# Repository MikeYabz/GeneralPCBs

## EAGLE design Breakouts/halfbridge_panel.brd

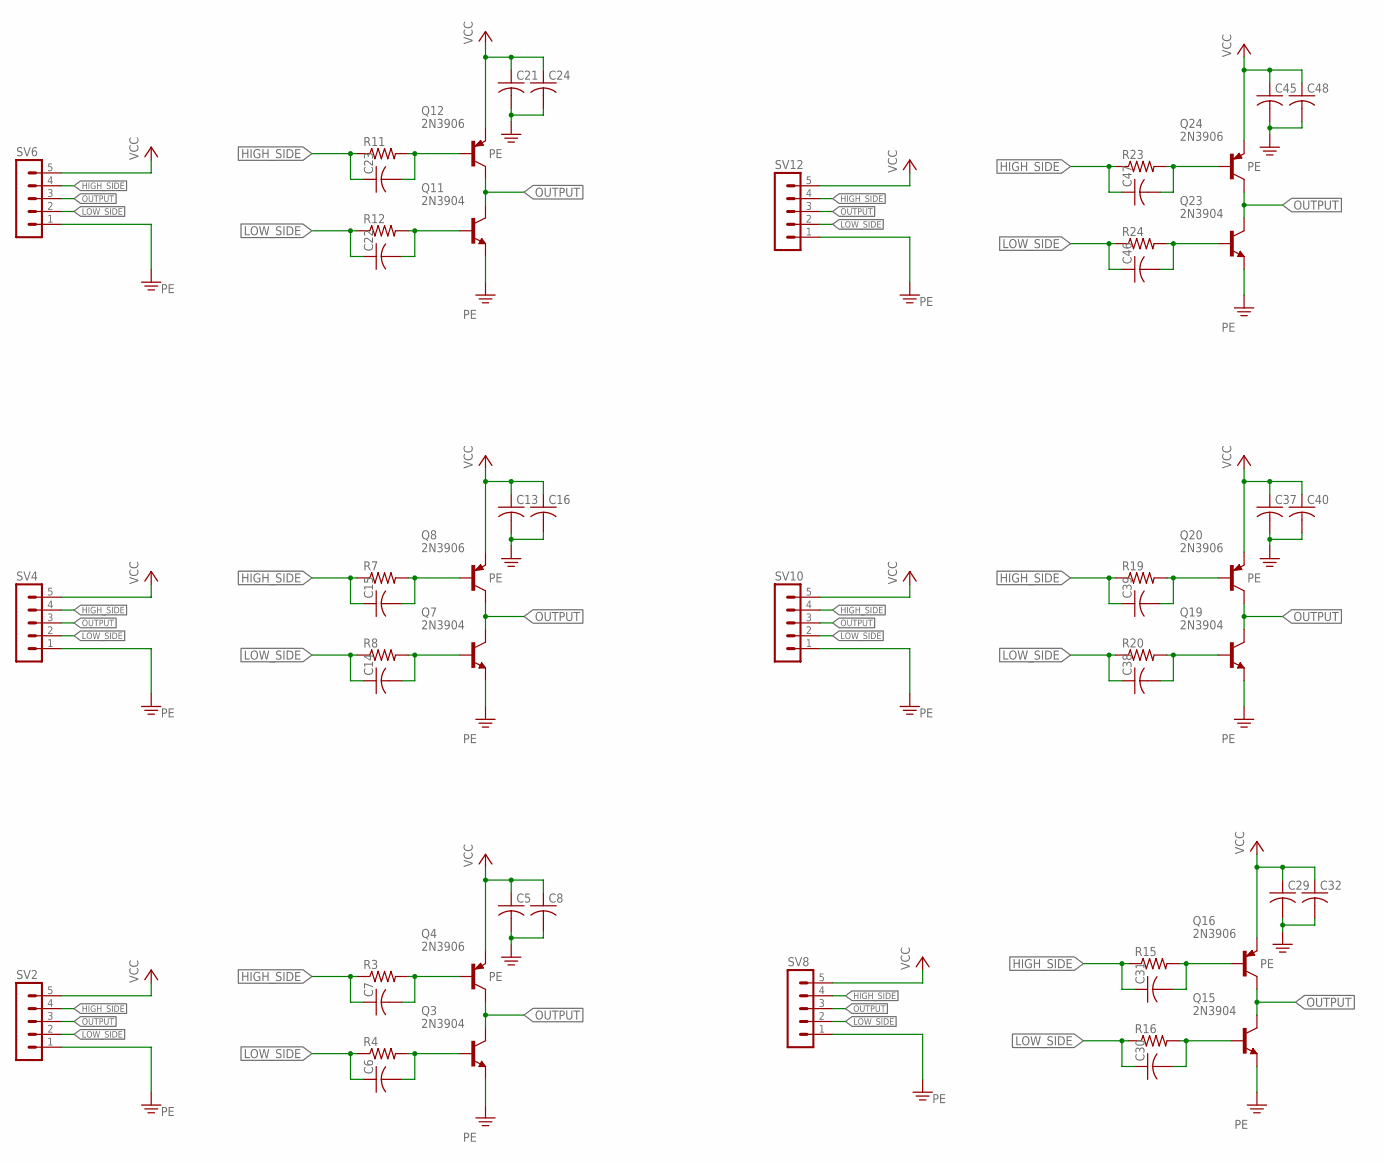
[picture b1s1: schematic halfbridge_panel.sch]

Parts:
C5, C6, C7, C8, C13, C14, C15, C16, C21, C22, C23, C24, C29, C30, C31, C32, C37, C38, C39, C40, C45, C46, C47, C48: C-US050-024X044; C050-024X044
Q3, Q7, Q11, Q15, Q19, Q23: 2N3904; TO-92
Q4, Q8, Q12, Q16, Q20, Q24: 2N3906; TO-92
R3, R4, R7, R8, R11, R12, R15, R16, R19, R20, R23, R24: R-US_0204/5; 0204/5
SV2, SV4, SV6, SV8, SV10, SV12: MA05-1

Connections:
HIGH_SIDE: C7.1, C15.1, C23.1, C31.1, C39.1, C47.1, R3.1, R7.1, R11.1, R15.1, R19.1, R23.1, SV2.4, SV4.4, SV6.4, SV8.4, SV10.4, SV12.4
LOW_SIDE: C6.1, C14.1, C22.1, C30.1, C38.1, C46.1, R4.1, R8.1, R12.1, R16.1, R20.1, R24.1, SV2.2, SV4.2, SV6.2, SV8.2, SV10.2, SV12.2
unnamed: C7.2, Q4.B, R3.2
unnamed: C6.2, Q3.B, R4.2
unnamed: C15.2, Q8.B, R7.2
unnamed: C14.2, Q7.B, R8.2
unnamed: C23.2, Q12.B, R11.2
unnamed: C22.2, Q11.B, R12.2
unnamed: C31.2, Q16.B, R15.2
unnamed: C30.2, Q15.B, R16.2
unnamed: C39.2, Q20.B, R19.2
unnamed: C38.2, Q19.B, R20.2
unnamed: C47.2, Q24.B, R23.2
unnamed: C46.2, Q23.B, R24.2
OUTPUT: Q3.C, Q4.C, Q7.C, Q8.C, Q11.C, Q12.C, Q15.C, Q16.C, Q19.C, Q20.C, Q23.C, Q24.C, SV2.3, SV4.3, SV6.3, SV8.3, SV10.3, SV12.3
PE: C5.2, C8.2, C13.2, C16.2, C21.2, C24.2, C29.2, C32.2, C37.2, C40.2, C45.2, C48.2, Q3.E, Q7.E, Q11.E, Q15.E, Q19.E, Q23.E, SV2.1, SV4.1, SV6.1, SV8.1, SV10.1, SV12.1
VCC: C5.1, C8.1, C13.1, C16.1, C21.1, C24.1, C29.1, C32.1, C37.1, C40.1, C45.1, C48.1, Q4.E, Q8.E, Q12.E, Q16.E, Q20.E, Q24.E, SV2.5, SV4.5, SV6.5, SV8.5, SV10.5, SV12.5

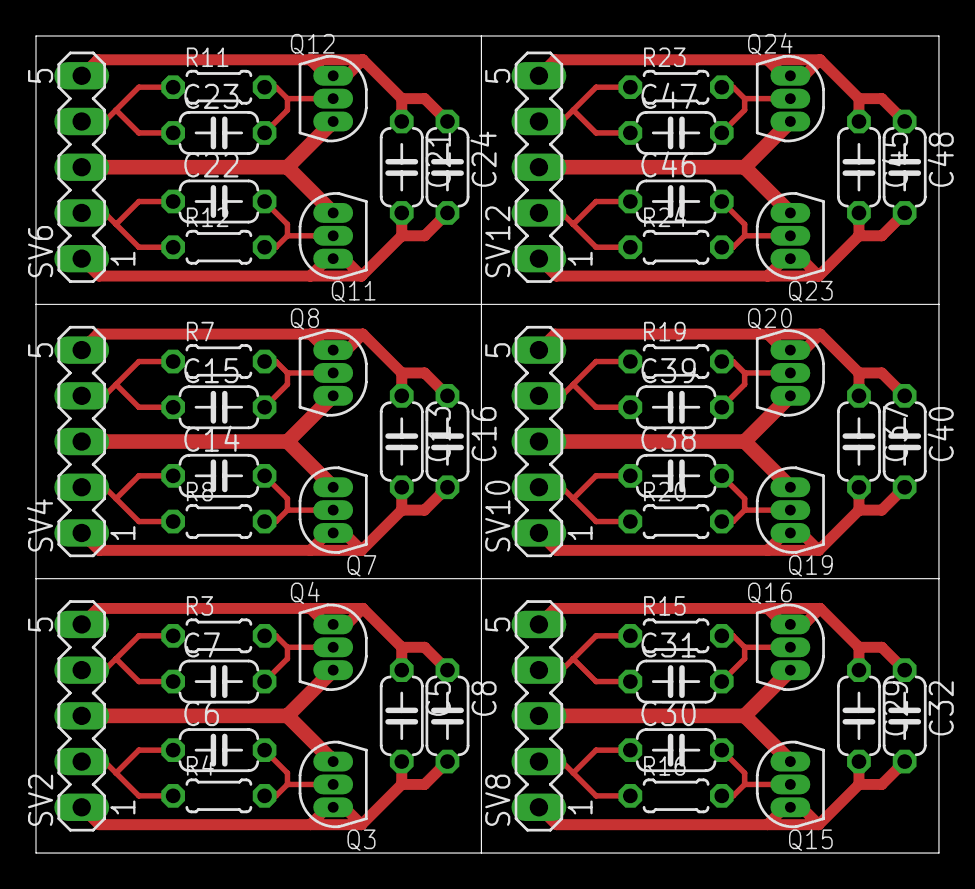
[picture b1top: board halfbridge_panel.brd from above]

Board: 2 copper layers, 50.2 x 45.4 mm, 54 parts (0 on the bottom side), 17 nets.

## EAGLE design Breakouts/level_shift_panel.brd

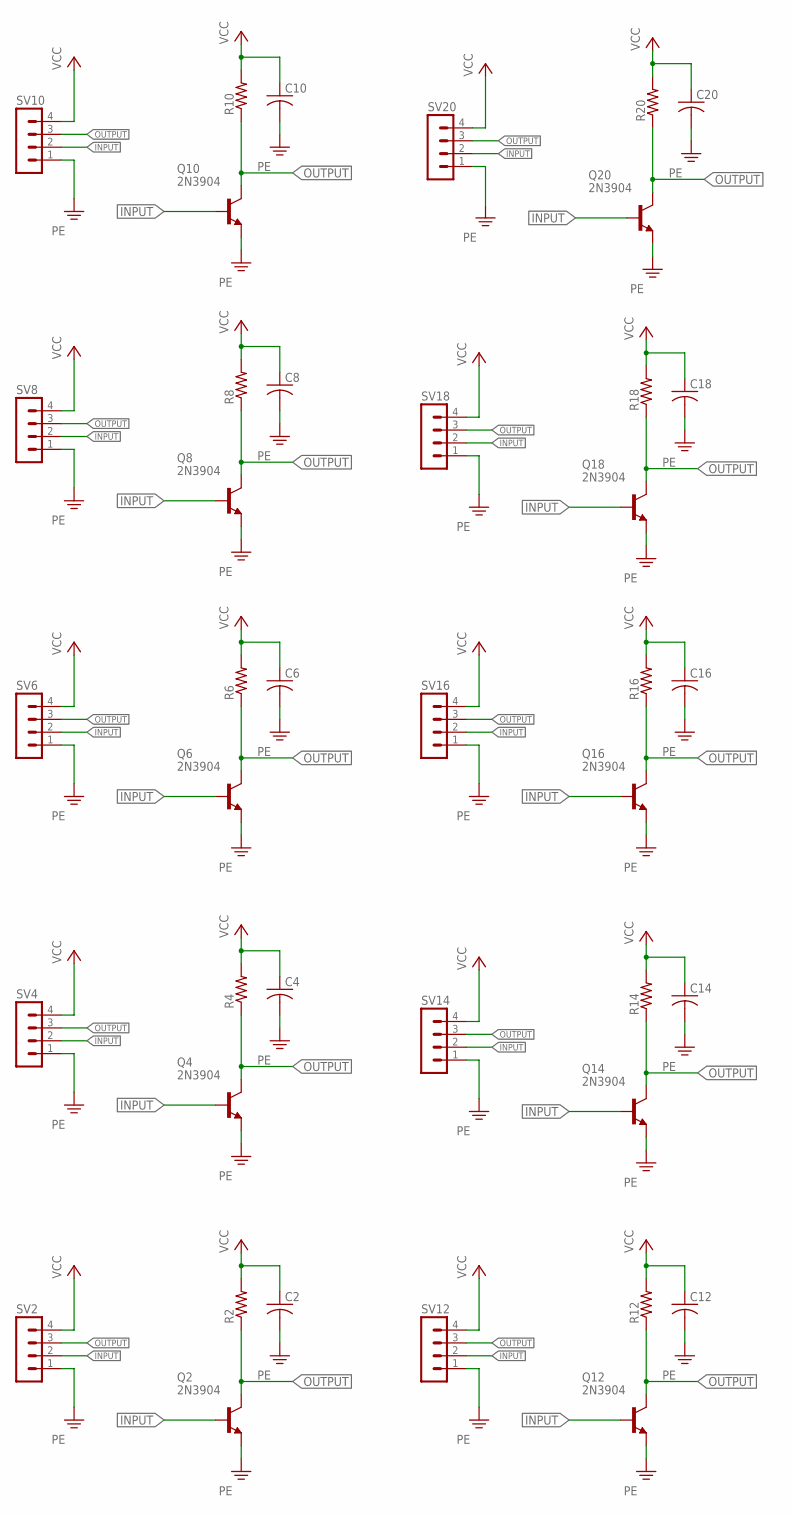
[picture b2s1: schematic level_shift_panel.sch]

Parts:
C2, C4, C6, C8, C10, C12, C14, C16, C18, C20: C-US025-030X050; C025-030X050
Q2, Q4, Q6, Q8, Q10, Q12, Q14, Q16, Q18, Q20: 2N3904; TO-92
R2, R4, R6, R8, R10, R12, R14, R16, R18, R20: R-US_0204/7; 0204/7
SV2, SV4, SV6, SV8, SV10, SV12, SV14, SV16, SV18, SV20: MA04-1

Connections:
INPUT: Q2.B, Q4.B, Q6.B, Q8.B, Q10.B, Q12.B, Q14.B, Q16.B, Q18.B, Q20.B, SV2.2, SV4.2, SV6.2, SV8.2, SV10.2, SV12.2, SV14.2, SV16.2, SV18.2, SV20.2
OUTPUT: Q2.C, Q4.C, Q6.C, Q8.C, Q10.C, Q12.C, Q14.C, Q16.C, Q18.C, Q20.C, R2.1, R4.1, R6.1, R8.1, R10.1, R12.1, R14.1, R16.1, R18.1, R20.1, SV2.3, SV4.3, SV6.3, SV8.3, SV10.3, SV12.3, SV14.3, SV16.3, SV18.3, SV20.3
PE: C2.2, C4.2, C6.2, C8.2, C10.2, C12.2, C14.2, C16.2, C18.2, C20.2, Q2.E, Q4.E, Q6.E, Q8.E, Q10.E, Q12.E, Q14.E, Q16.E, Q18.E, Q20.E, SV2.1, SV4.1, SV6.1, SV8.1, SV10.1, SV12.1, SV14.1, SV16.1, SV18.1, SV20.1
VCC: C2.1, C4.1, C6.1, C8.1, C10.1, C12.1, C14.1, C16.1, C18.1, C20.1, R2.2, R4.2, R6.2, R8.2, R10.2, R12.2, R14.2, R16.2, R18.2, R20.2, SV2.4, SV4.4, SV6.4, SV8.4, SV10.4, SV12.4, SV14.4, SV16.4, SV18.4, SV20.4

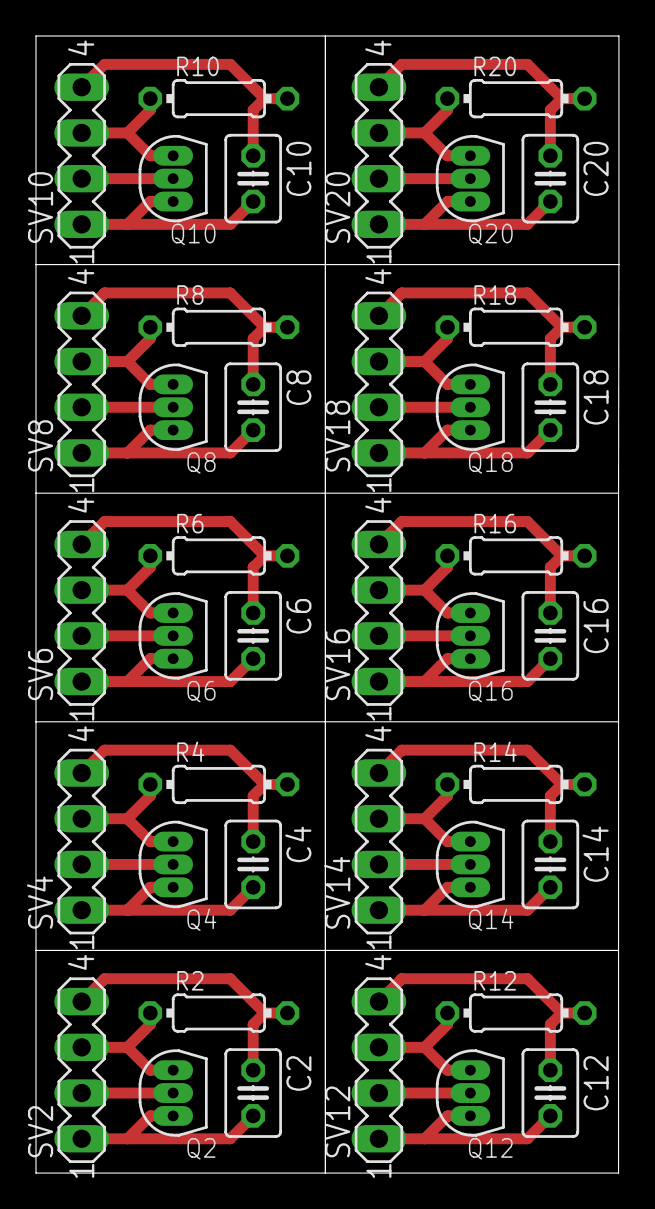
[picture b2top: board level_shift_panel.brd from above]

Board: 2 copper layers, 32.4 x 63.2 mm, 40 parts (0 on the bottom side), 4 nets.

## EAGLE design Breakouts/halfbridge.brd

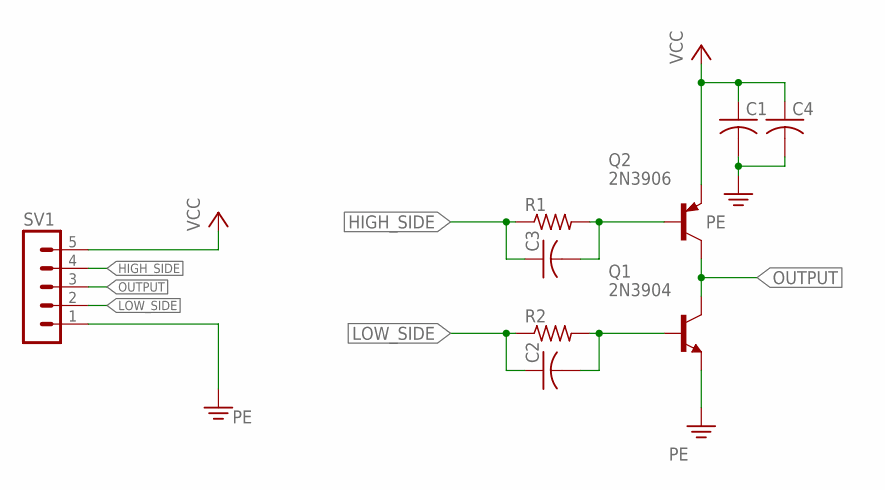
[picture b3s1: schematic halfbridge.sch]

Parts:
C1, C2, C3, C4: C-US050-024X044; C050-024X044
Q1: 2N3904; TO-92
Q2: 2N3906; TO-92
R1, R2: R-US_0204/5; 0204/5
SV1: MA05-1

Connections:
HIGH_SIDE: C3.1, R1.1, SV1.4
LOW_SIDE: C2.1, R2.1, SV1.2
unnamed: C3.2, Q2.B, R1.2
unnamed: C2.2, Q1.B, R2.2
OUTPUT: Q1.C, Q2.C, SV1.3
PE: C1.2, C4.2, Q1.E, SV1.1
VCC: C1.1, C4.1, Q2.E, SV1.5

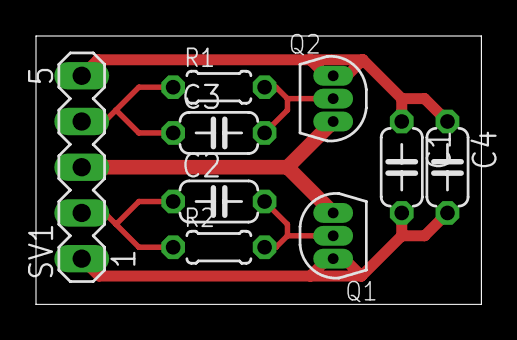
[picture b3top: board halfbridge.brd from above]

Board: 2 copper layers, 24.7 x 14.9 mm, 9 parts (0 on the bottom side), 7 nets.

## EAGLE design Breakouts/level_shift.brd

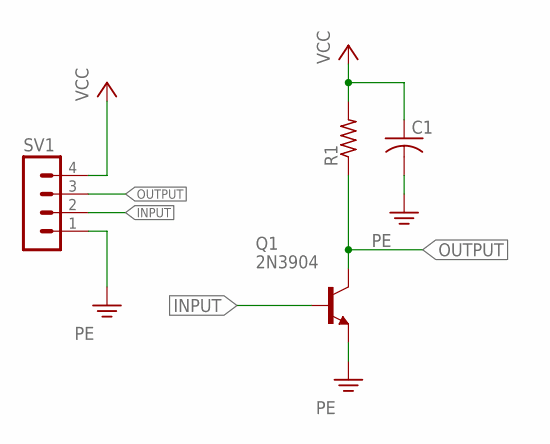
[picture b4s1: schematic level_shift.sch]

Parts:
C1: C-US025-030X050; C025-030X050
Q1: 2N3904; TO-92
R1: R-US_0204/7; 0204/7
SV1: MA04-1

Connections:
INPUT: Q1.B, SV1.2
OUTPUT: Q1.C, R1.1, SV1.3
PE: C1.2, Q1.E, SV1.1
VCC: C1.1, R1.2, SV1.4

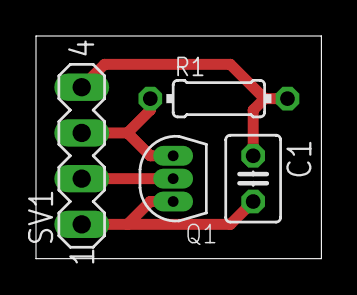
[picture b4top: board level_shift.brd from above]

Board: 2 copper layers, 15.9 x 12.4 mm, 4 parts (0 on the bottom side), 4 nets.

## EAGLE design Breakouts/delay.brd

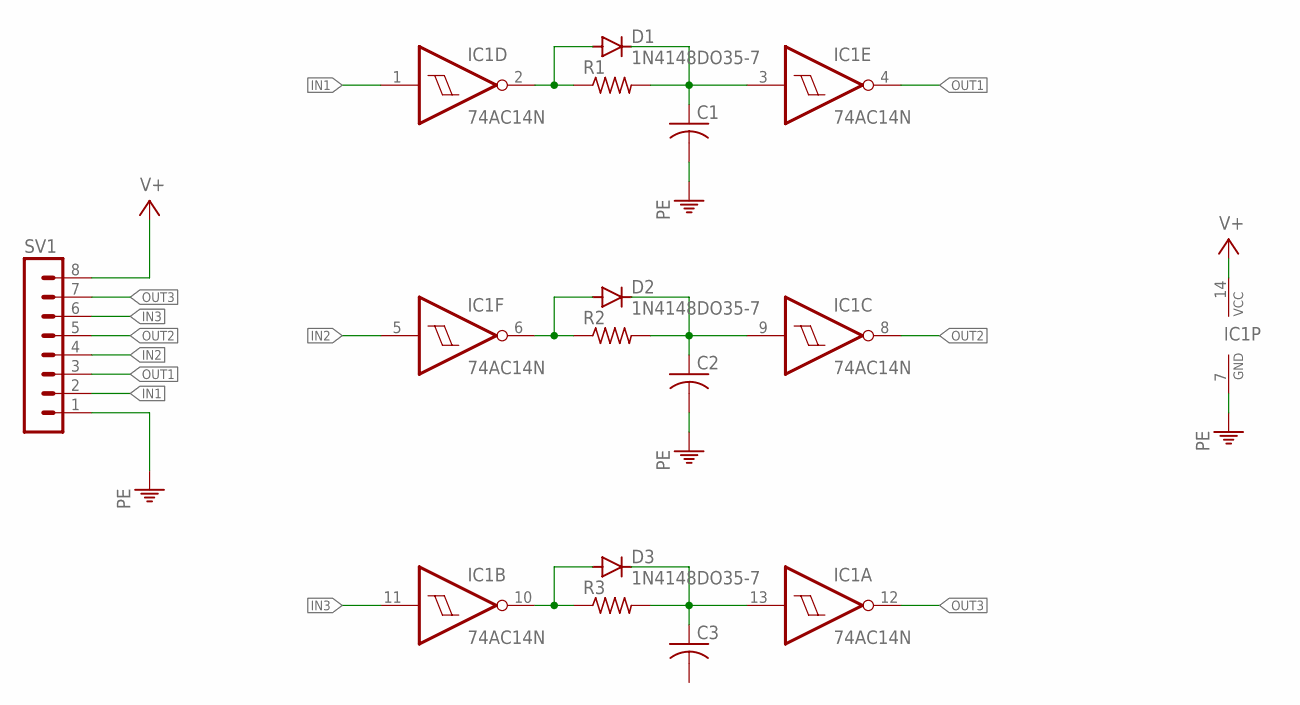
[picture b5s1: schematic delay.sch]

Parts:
C1, C2, C3: C-US025-025X050; C025-025X050
D1, D2, D3: 1N4148DO35-7; DO35-7
IC1: 74AC14N; DIL14
R1, R2, R3: R-US_0204/7; 0204/7
SV1: MA08-1

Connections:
IN1: IC1.1 (I), SV1.2
IN2: IC1.5 (I), SV1.4
IN3: IC1.11 (I), SV1.6
unnamed: C1.1, D1.C, IC1.3 (I), R1.2
unnamed: D1.A, IC1.2 (O), R1.1
unnamed: C2.1, D2.C, IC1.9 (I), R2.2
unnamed: D2.A, IC1.6 (O), R2.1
unnamed: C3.1, D3.C, IC1.13 (I), R3.2
unnamed: D3.A, IC1.10 (O), R3.1
OUT1: IC1.4 (O), SV1.3
OUT2: IC1.8 (O), SV1.5
OUT3: IC1.12 (O), SV1.7
PE: C1.2, C2.2, IC1.7 (GND), SV1.1
V+: IC1.14 (VCC), SV1.8

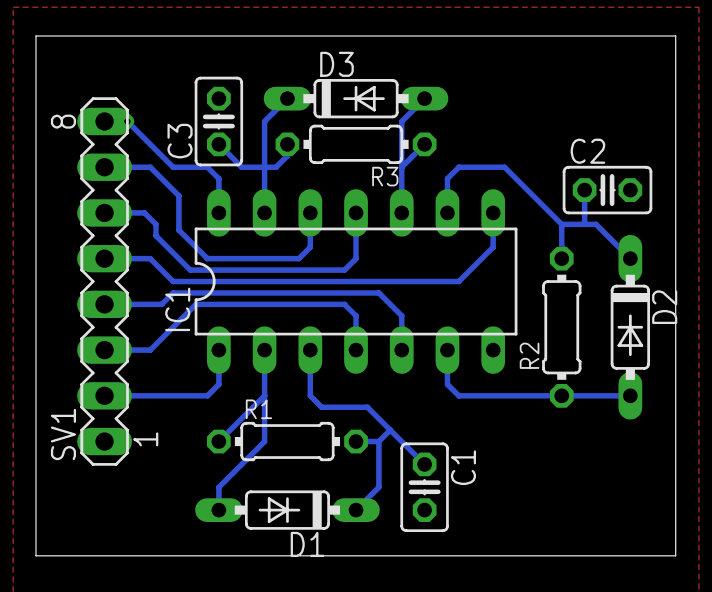
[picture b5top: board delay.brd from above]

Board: 2 copper layers, 35.5 x 28.9 mm, 11 parts (0 on the bottom side), 14 nets.

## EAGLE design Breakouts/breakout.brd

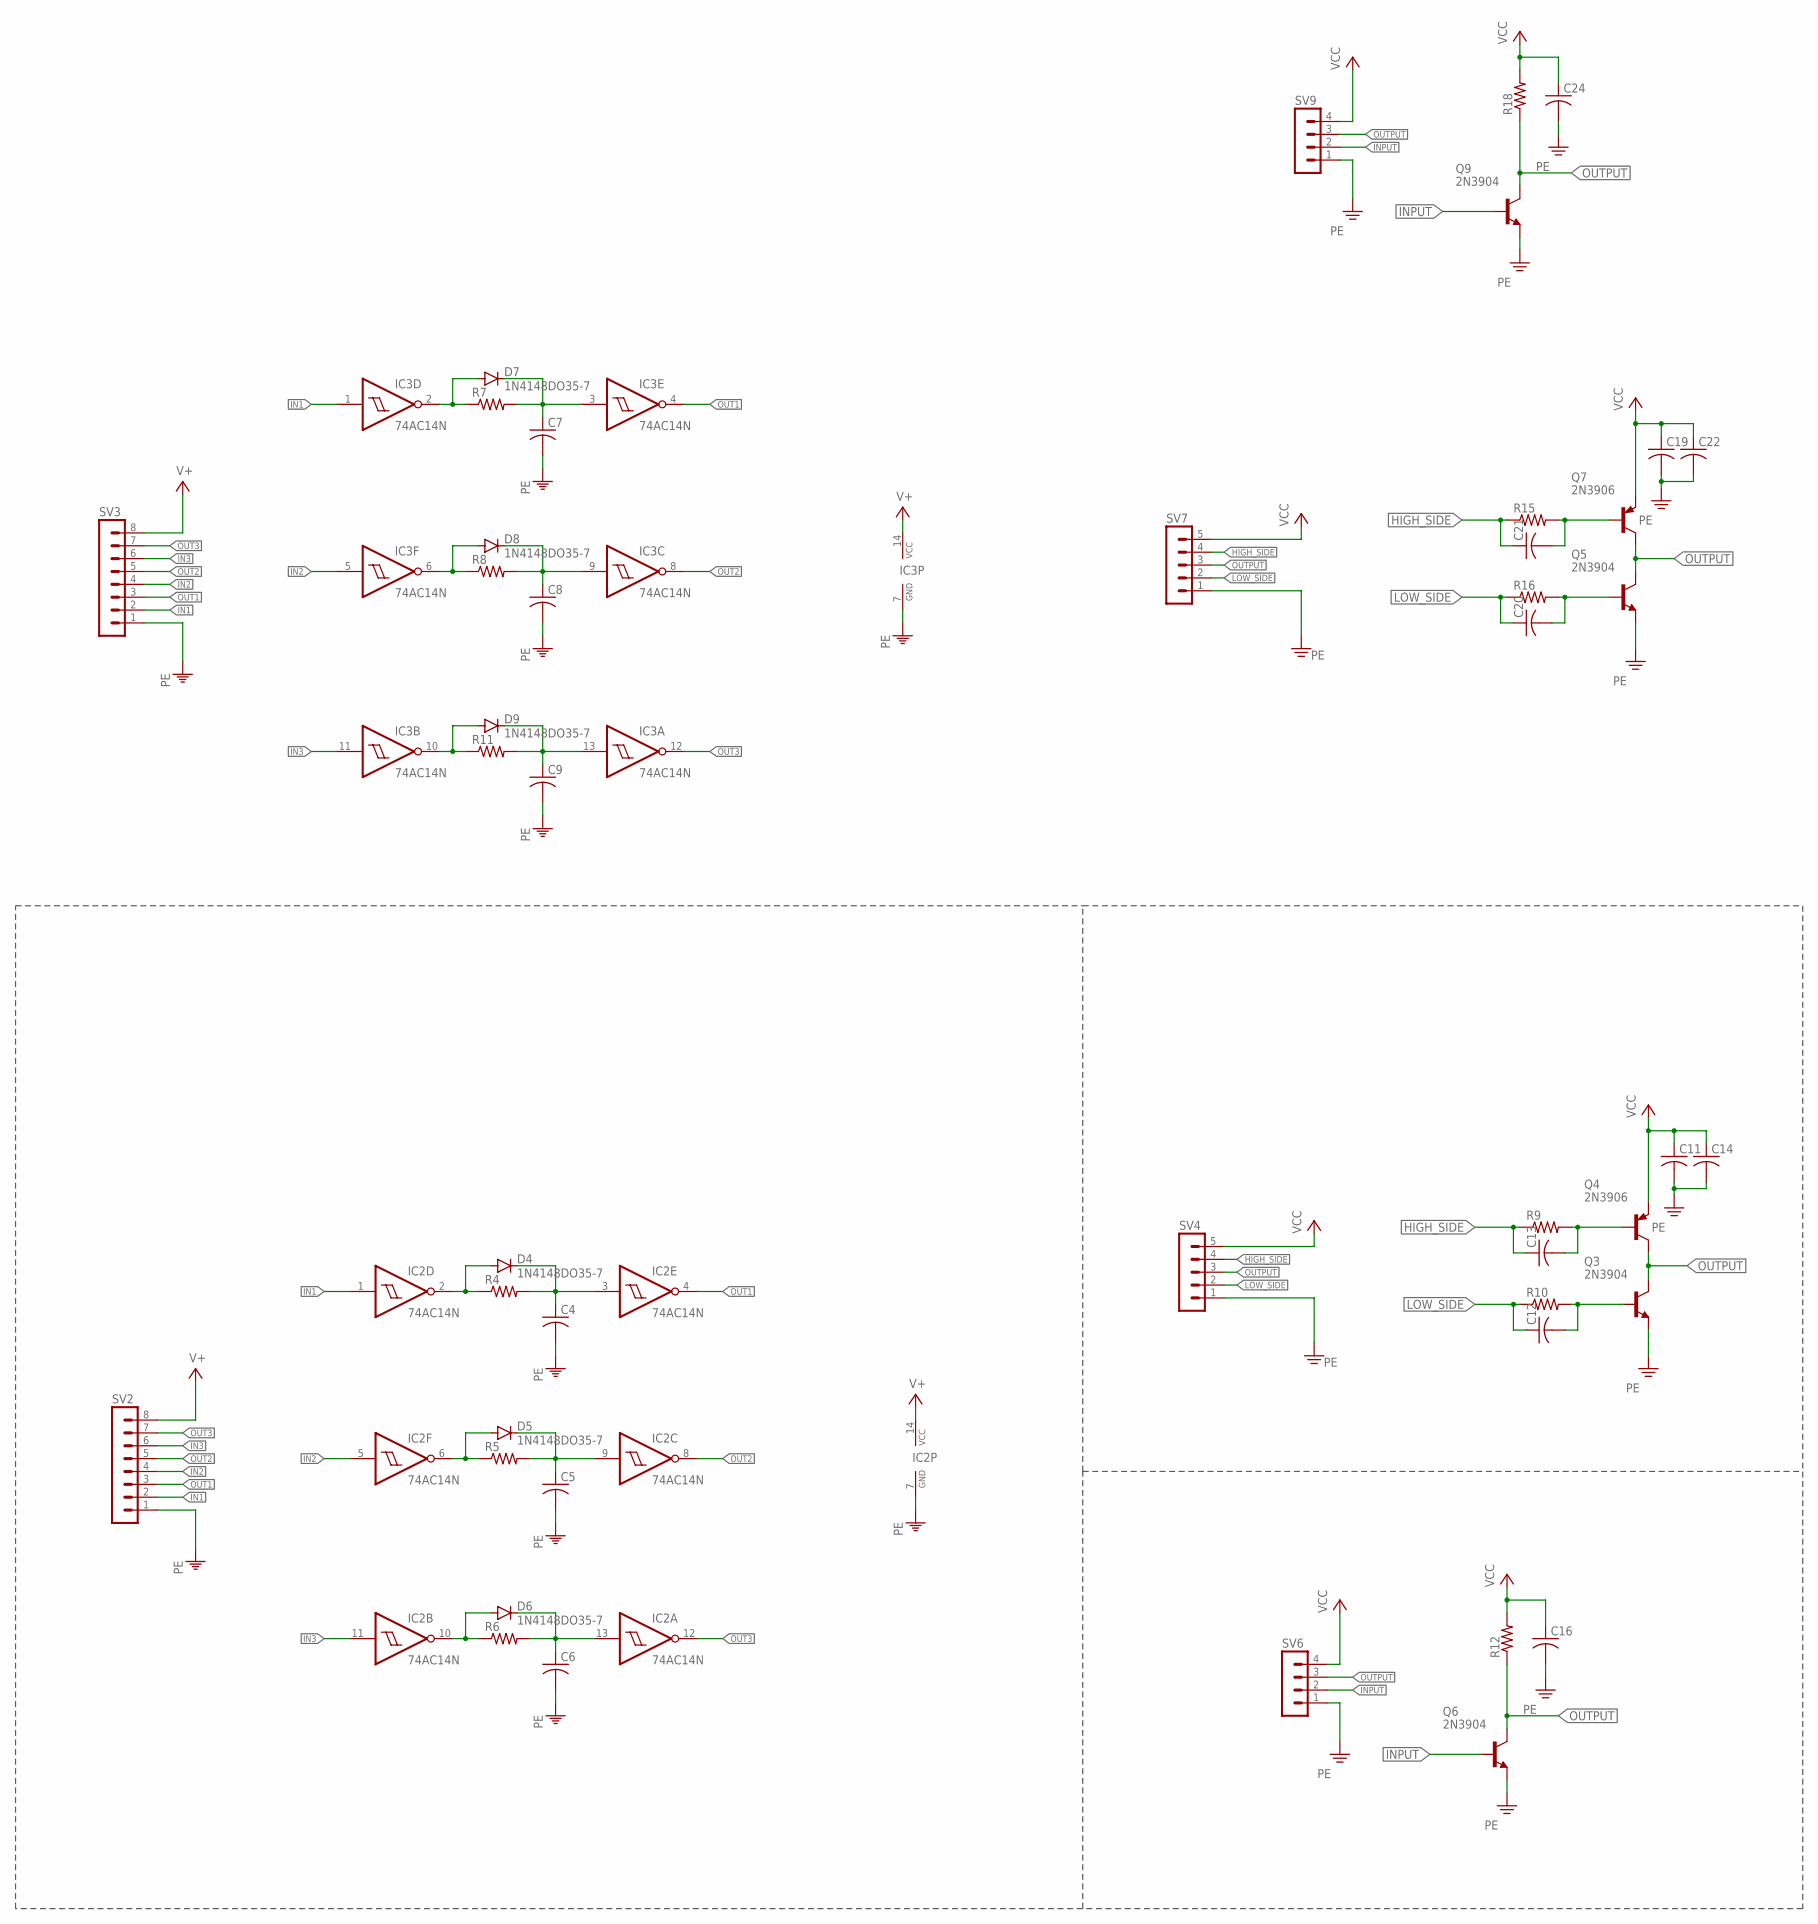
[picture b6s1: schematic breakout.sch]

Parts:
C4, C5, C6, C7, C8, C9: C-US025-025X050; C025-025X050
C11, C12, C13, C14, C19, C20, C21, C22: C-US050-024X044; C050-024X044
C16, C24: C-US025-030X050; C025-030X050
D4, D5, D6, D7, D8, D9: 1N4148DO35-7; DO35-7
IC2, IC3: 74AC14N; DIL14
Q3, Q5, Q6, Q9: 2N3904; TO-92
Q4, Q7: 2N3906; TO-92
R4, R5, R6, R7, R8, R11, R12, R18: R-US_0204/7; 0204/7
R9, R10, R15, R16: R-US_0204/5; 0204/5
SV2, SV3: MA08-1
SV4, SV7: MA05-1
SV6, SV9: MA04-1

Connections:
HIGH_SIDE: C13.1, C21.1, R9.1, R15.1, SV4.4, SV7.4
IN1: IC2.1 (I), IC3.1 (I), SV2.2, SV3.2
IN2: IC2.5 (I), IC3.5 (I), SV2.4, SV3.4
IN3: IC2.11 (I), IC3.11 (I), SV2.6, SV3.6
INPUT: Q6.B, Q9.B, SV6.2, SV9.2
LOW_SIDE: C12.1, C20.1, R10.1, R16.1, SV4.2, SV7.2
unnamed: C4.1, D4.C, IC2.3 (I), R4.2
unnamed: D4.A, IC2.2 (O), R4.1
unnamed: C5.1, D5.C, IC2.9 (I), R5.2
unnamed: D5.A, IC2.6 (O), R5.1
unnamed: C6.1, D6.C, IC2.13 (I), R6.2
unnamed: D6.A, IC2.10 (O), R6.1
unnamed: C7.1, D7.C, IC3.3 (I), R7.2
unnamed: D7.A, IC3.2 (O), R7.1
unnamed: C13.2, Q4.B, R9.2
unnamed: C12.2, Q3.B, R10.2
unnamed: C8.1, D8.C, IC3.9 (I), R8.2
unnamed: D8.A, IC3.6 (O), R8.1
unnamed: C9.1, D9.C, IC3.13 (I), R11.2
unnamed: D9.A, IC3.10 (O), R11.1
unnamed: C21.2, Q7.B, R15.2
unnamed: C20.2, Q5.B, R16.2
OUT1: IC2.4 (O), IC3.4 (O), SV2.3, SV3.3
OUT2: IC2.8 (O), IC3.8 (O), SV2.5, SV3.5
OUT3: IC2.12 (O), IC3.12 (O), SV2.7, SV3.7
OUTPUT: Q3.C, Q4.C, Q5.C, Q6.C, Q7.C, Q9.C, R12.1, R18.1, SV4.3, SV6.3, SV7.3, SV9.3
PE: C4.2, C5.2, C6.2, C7.2, C8.2, C9.2, C11.2, C14.2, C16.2, C19.2, C22.2, C24.2, IC2.7 (GND), IC3.7 (GND), Q3.E, Q5.E, Q6.E, Q9.E, SV2.1, SV3.1, SV4.1, SV6.1, SV7.1, SV9.1
V+: IC2.14 (VCC), IC3.14 (VCC), SV2.8, SV3.8
VCC: C11.1, C14.1, C16.1, C19.1, C22.1, C24.1, Q4.E, Q7.E, R12.2, R18.2, SV4.5, SV6.4, SV7.5, SV9.4

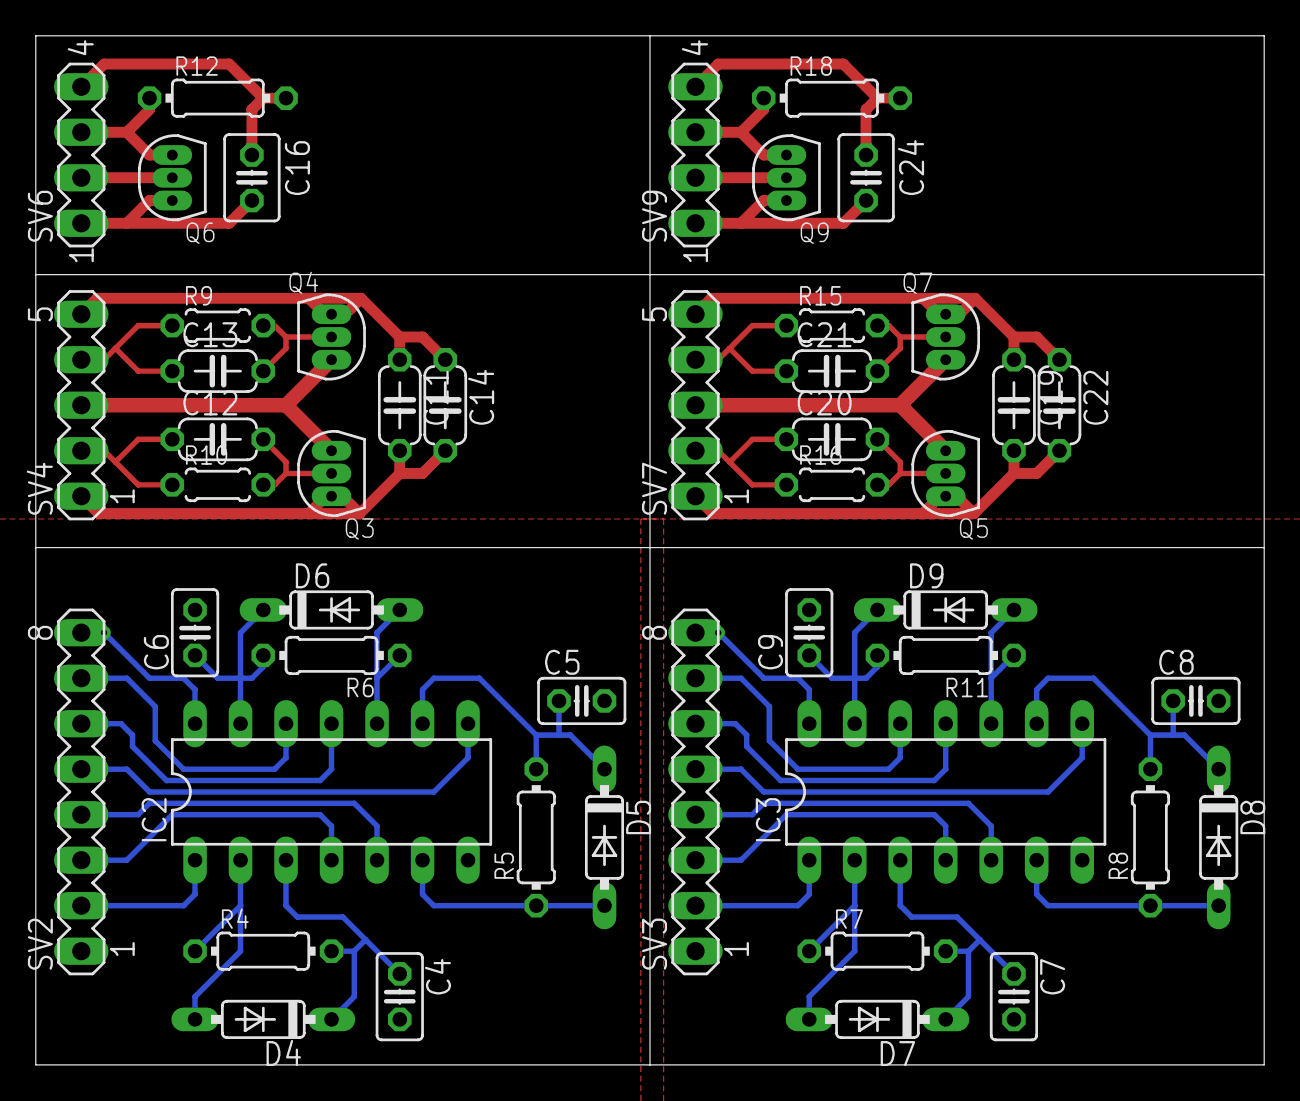
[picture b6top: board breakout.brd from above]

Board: 2 copper layers, 68.6 x 57.5 mm, 48 parts (0 on the bottom side), 29 nets.

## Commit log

2019-10-08 production files
2019-10-08 added panels
